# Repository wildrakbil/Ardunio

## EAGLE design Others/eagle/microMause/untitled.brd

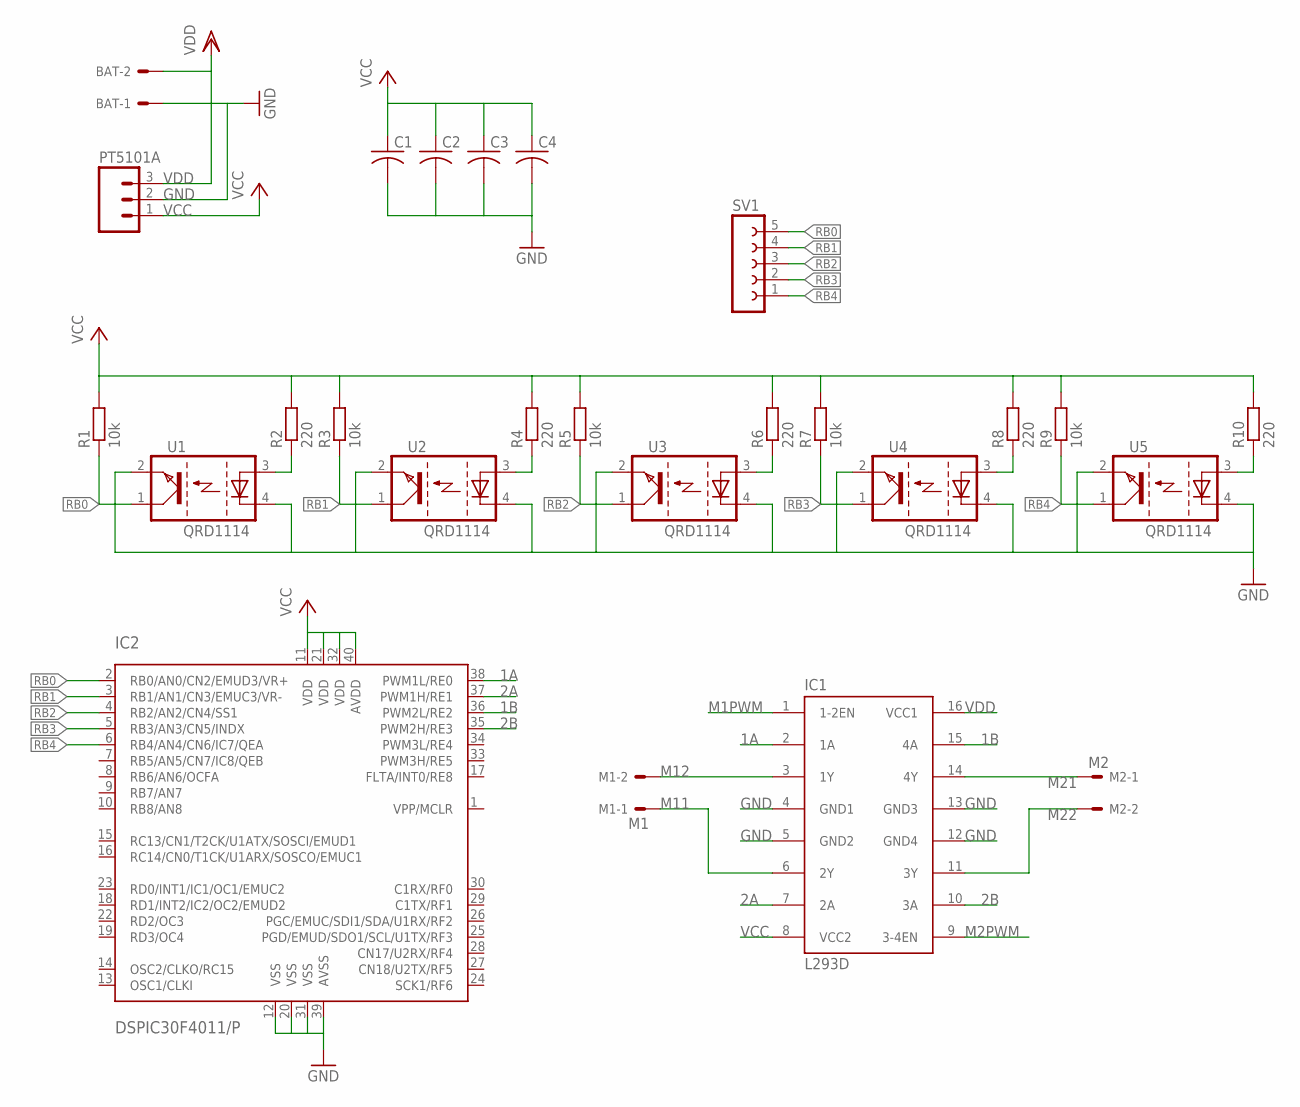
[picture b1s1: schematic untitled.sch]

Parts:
BAT: 22-27-2021-02; 6410-02
C1, C2, C3, C4: C-US025-024X044; C025-024X044
IC1: L293D; DIL16
IC2: DSPIC30F4011/P; DIL40
M1: M1; 6410-02
M2: M2; 6410-02
PT5101A: M03; 03P
R1, R3, R5, R7, R9: 10k; 0204/5
R2, R4, R6, R8, R10: 220; 0204/5
SV1: FE05-1
U1, U2, U3, U4, U5: QRD1114

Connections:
1A: IC1.2 (1A), IC2.38 (PWM1L/RE0)
1B: IC1.15 (4A), IC2.36 (PWM2L/RE2)
2A: IC1.7 (2A), IC2.37 (PWM1H/RE1)
2B: IC1.10 (3A), IC2.35 (PWM2H/RE3)
GND: BAT.1, C1.2, C2.2, C3.2, C4.2, IC1.4 (GND1), IC1.5 (GND2), IC1.12 (GND4), IC1.13 (GND3), IC2.12 (VSS), IC2.20 (VSS), IC2.31 (VSS), IC2.39 (AVSS), PT5101A.2, U1.2, U1.4, U2.2, U2.4, U3.2, U3.4, U4.2, U4.4, U5.2, U5.4
M1PWM: IC1.1 (1-2EN)
M2PWM: IC1.9 (3-4EN)
M11: IC1.6 (2Y), M1.1
M12: IC1.3 (1Y), M1.2
M21: IC1.14 (4Y), M2.1
M22: IC1.11 (3Y), M2.2
unnamed: R2.1, U1.3
unnamed: R4.1, U2.3
unnamed: R10.1, U5.3
unnamed: R6.1, U3.3
unnamed: R8.1, U4.3
RB0: IC2.2 (RB0/AN0/CN2/EMUD3/VR+), R1.1, SV1.5, U1.1
RB1: IC2.3 (RB1/AN1/CN3/EMUC3/VR-), R3.1, SV1.4, U2.1
RB2: IC2.4 (RB2/AN2/CN4/SS1), R5.1, SV1.3, U3.1
RB3: IC2.5 (RB3/AN3/CN5/INDX), R7.1, SV1.2, U4.1
RB4: IC2.6 (RB4/AN4/CN6/IC7/QEA), R9.1, SV1.1, U5.1
VCC: C1.1, C2.1, C3.1, C4.1, IC1.8 (VCC2), IC2.11 (VDD), IC2.21 (VDD), IC2.32 (VDD), IC2.40 (AVDD), PT5101A.1, R1.2, R2.2, R3.2, R4.2, R5.2, R6.2, R7.2, R8.2, R9.2, R10.2
VDD: BAT.2, IC1.16 (VCC1), PT5101A.3

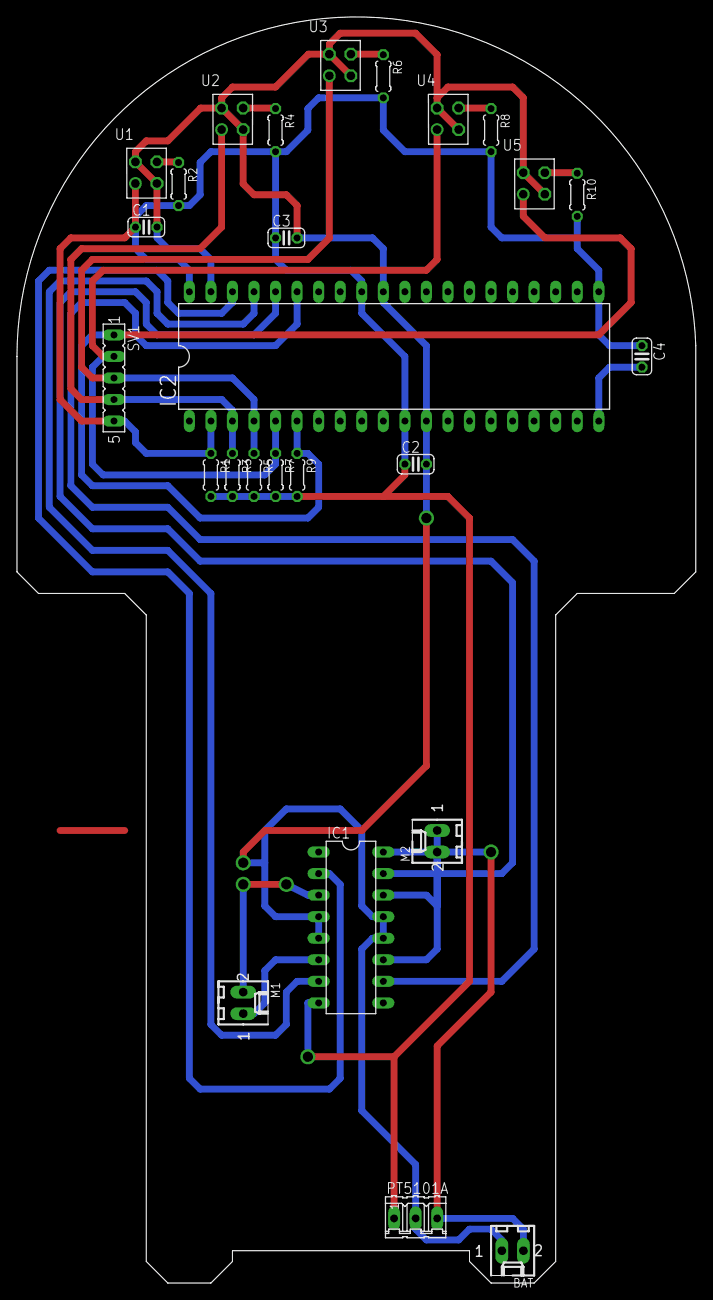
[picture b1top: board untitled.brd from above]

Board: 2 copper layers, 80.0 x 149.2 mm, 26 parts (0 on the bottom side), 21 nets.

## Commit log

2021-01-14 Base Code for Arduino boards
2021-01-15 Ajuste del sistema de nivel de agua
